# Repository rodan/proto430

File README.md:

## proto430

 ////// UNDER DEVELOPMENT ///////////////////////

 BoosterPack-compatible development boards used for quick prototyping and interfacing with i2c/spi/uart-based devices

```
 source:       https://github.com/rodan/proto430
 author:       Petre Rodan <2b4eda@subdimension.ro>
 license:      BSD
```

### Components

Collection of plug-in Booster-Pack PCBs compatible with the Texas Instruments LaunchPad development ecosystem. one board provides access to any 3v3 device via a serial interface, the other brings access to a graphical VFD display, a rotary encoder and also has infrared remote input. the two will be linked via i2c or spi.

project directory structure

 * ./hardware/display.* - eagle-based schematics and pcbs for the spi-based Noritake VFD 
 * ./hardware/sensor.*  - eagle-based schematics and pcbs for the i2c/spi/uart devboard
 * ./hardware/vfd.* - firmware for the display pcb

testing is done with MSP-EXP430FR5994 development kits

### Build requirements

you will need TI's excelent [GCC toolchain](https://www.ti.com/tool/MSP430-GCC-OPENSOURCE) or Code Composer Studio for linux and my [reference libraries for msp430 micros](https://github.com/rodan/atlas430) cloned in /opt/.

```
cd ./firmware
make
make install
```

the devboard has been modified by adding a 16MHz high frequency crystal and two load capacitors. if these components are missing from your board then make sure to disable the *USE_XT2* define from the Makefile or CCS.

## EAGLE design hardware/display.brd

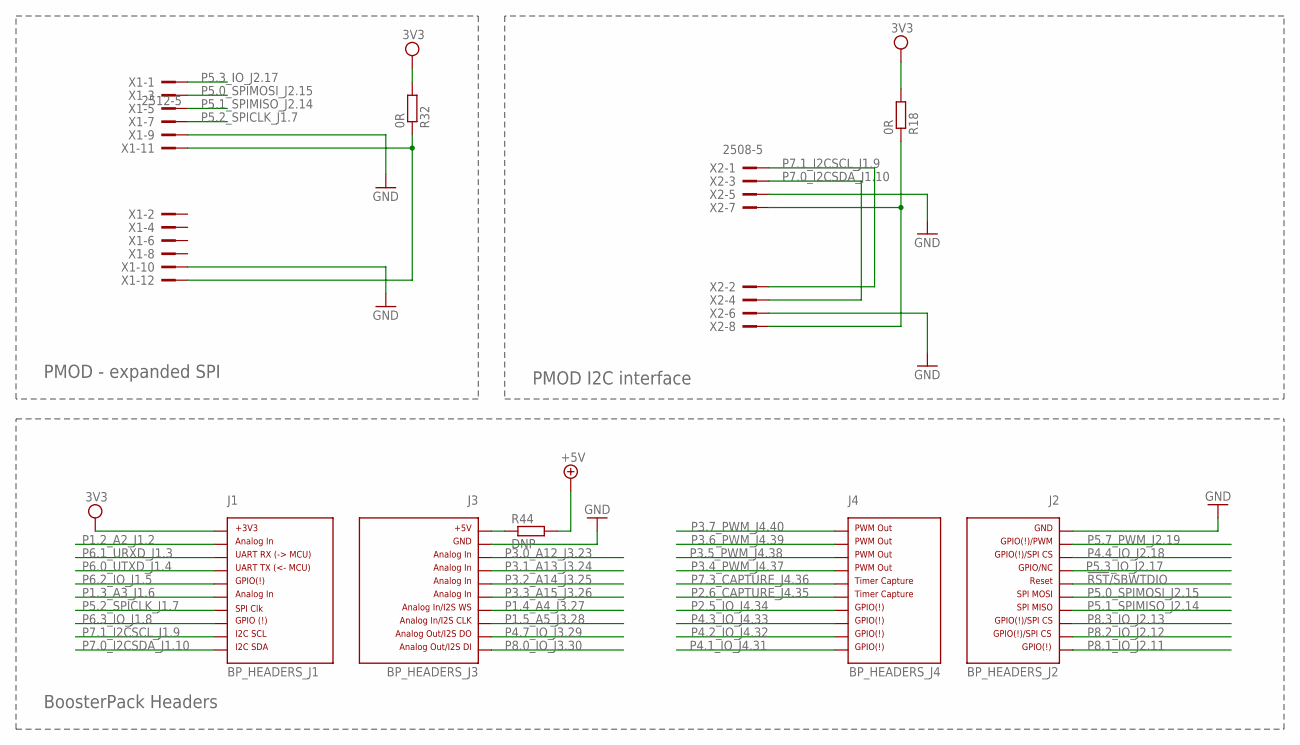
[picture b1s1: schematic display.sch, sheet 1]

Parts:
J1: BP_HEADERS_J1; J1
J2: BP_HEADERS_J2; J2
J3: BP_HEADERS_J3; J3
J4: BP_HEADERS_J4; J4
R18, R32: 0R; 0204V
R44: DNP; R0805W
X1: 2512-5; PAK100/2500-5-12
X2: 2508-5; PAK100/2500-5-08

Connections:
3V3: J1.1, R18.2, R32.2; also elsewhere on the board
!RST!/SBWTDIO: J2.16
+5V: R44.2; also elsewhere on the board
GND: J2.20, J3.22, X1.9, X1.10, X2.5, X2.6; also elsewhere on the board
unnamed: R18.1, X2.7, X2.8
unnamed: R32.1, X1.11, X1.12
unnamed: J3.21, R44.1
P1.2_A2_J1.2: J1.2; also elsewhere on the board
P1.3_A3_J1.6: J1.6; also elsewhere on the board
P1.4_A4_J3.27: J3.27; also elsewhere on the board
P1.5_A5_J3.28: J3.28; also elsewhere on the board
P2.5_IO_J4.34: J4.34; also elsewhere on the board
P2.6_CAPTURE_J4.35: J4.35; also elsewhere on the board
P3.0_A12_J3.23: J3.23; also elsewhere on the board
P3.1_A13_J3.24: J3.24; also elsewhere on the board
P3.2_A14_J3.25: J3.25; also elsewhere on the board
P3.3_A15_J3.26: J3.26; also elsewhere on the board
P3.4_PWM_J4.37: J4.37
P3.5_PWM_J4.38: J4.38
P3.6_PWM_J4.39: J4.39
P3.7_PWM_J4.40: J4.40
P4.1_IO_J4.31: J4.31
P4.2_IO_J4.32: J4.32
P4.3_IO_J4.33: J4.33
P4.4_IO_J2.18: J2.18; also elsewhere on the board
P4.7_IO_J3.29: J3.29
P5.0_SPIMOSI_J2.15: J2.15, X1.3; also elsewhere on the board
P5.1_SPIMISO_J2.14: J2.14, X1.5; also elsewhere on the board
P5.2_SPICLK_J1.7: J1.7, X1.7; also elsewhere on the board
P5.3_IO_J2.17: J2.17, X1.1
P5.7_PWM_J2.19: J2.19; also elsewhere on the board
P6.0_UTXD_J1.4: J1.4
P6.1_URXD_J1.3: J1.3
P6.2_IO_J1.5: J1.5
P6.3_IO_J1.8: J1.8; also elsewhere on the board
P7.0_I2CSDA_J1.10: J1.10, X2.3, X2.4; also elsewhere on the board
P7.1_I2CSCL_J1.9: J1.9, X2.1, X2.2; also elsewhere on the board
P7.3_CAPTURE_J4.36: J4.36; also elsewhere on the board
P8.0_IO_J3.30: J3.30
P8.1_IO_J2.11: J2.11; also elsewhere on the board
P8.2_IO_J2.12: J2.12; also elsewhere on the board
P8.3_IO_J2.13: J2.13; also elsewhere on the board

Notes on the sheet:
BoosterPack Headers
PMOD - expanded SPI
PMOD I2C interface

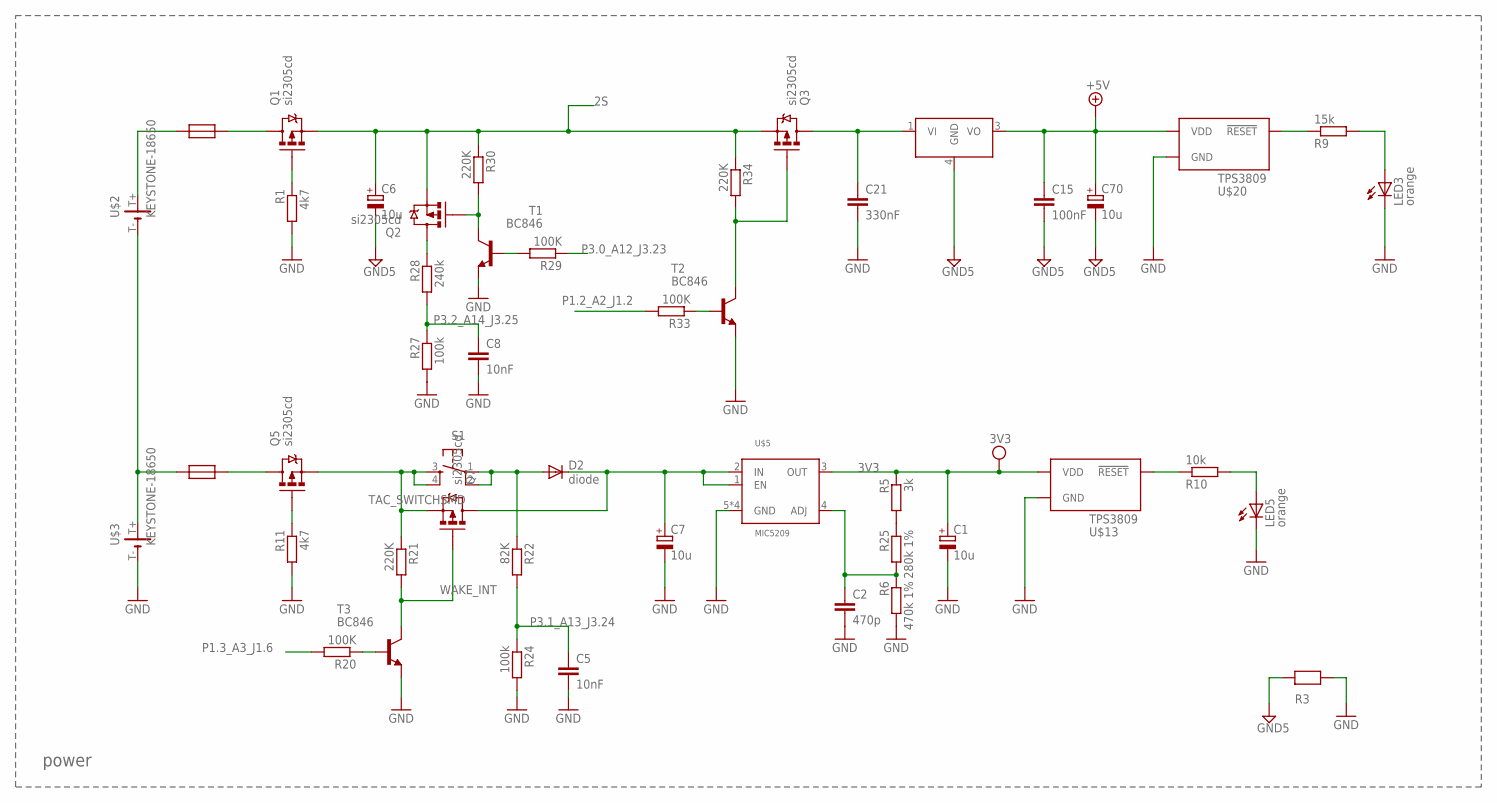
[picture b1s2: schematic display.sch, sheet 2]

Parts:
C1, C6, C7, C70: 10u; 153CLV-0405
C2: 470p; C0805
C5, C8: 10nF; C0805
C15: 100nF; C0805
C21: 330nF; C0805
D2: diode; SMA-DIODE
LED3, LED5: orange; CHIPLED_0805
Q1, Q2, Q3, Q5, Q7: si2305cd; SOT23-3_POWER
R1, R11: 4k7; R0805W
R3: 0R_0805; R0805W
R5: 3k; R0805W
R6: 470k 1%; R0805W
R9: 15k; R0805W
R10: 10k; R0805W
R20, R29, R33: 100K; R0805W
R21, R30, R34: 220K; R0805W
R22: 82K; R0805W
R24, R27: 100k; R0805W
R25: 280k 1%; R0805W
R28: 240k; R0805W
S1: TAC_SWITCHSMD; TACTILE-SWITCH-SMD
T1, T2, T3: BC846; SOT23
U4: 7805; D2PACK
U$2, U$3: KEYSTONE-18650; KEYSTONE_COMBO_18650
U$5: MIC5209; SO-08
U$7, U$8: Fuse 1A; 0805W
U$13, U$20: TPS3809; R_PDSO_G3

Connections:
2S: C6.+, Q1.2 (S), Q2.2 (S), Q3.2 (S), R30.1, R34.1; also elsewhere on the board
3V3: C1.+, R5.1, U$5.3 (OUT), U$13.P$3 (VDD); also elsewhere on the board
+5V: C15.1, C70.+, U4.3 (VO), U$20.P$3 (VDD); also elsewhere on the board
GND: C1.-, C2.2, C5.2, C7.-, C8.2, C21.2, LED3.C, LED5.C, R1.2, R3.2, R6.2, R11.2, R24.2, R27.2, T1.2 (E), T2.2 (E), T3.2 (E), U$3.T- (-), U$5.5 (GND), U$5.6 (GND), U$5.7 (GND), U$5.8 (GND), U$13.P$1 (GND), U$20.P$1 (GND); also elsewhere on the board
GND5: C6.-, C15.2, C70.-, R3.1, U4.4 (GND); also elsewhere on the board
unnamed: C21.1, Q3.3 (D), U4.1 (VI)
unnamed: Q1.1 (G), R1.1
unnamed: Q5.2 (S), Q7.2 (S), R21.1, S1.3, S1.4
unnamed: LED3.A, R9.2
unnamed: C2.1, R6.1, R25.2, U$5.4 (ADJ)
unnamed: Q1.3 (D), U$7.2
unnamed: Q5.3 (D), U$8.2
unnamed: R9.1, U$20.P$2 (!RESET)
unnamed: LED5.A, R10.2
unnamed: R10.1, U$13.P$2 (!RESET)
unnamed: C7.+, D2.C, Q7.3 (D), U$5.1 (EN), U$5.2 (IN)
unnamed: Q5.1 (G), R11.1
unnamed: R5.2, R25.1
unnamed: Q2.3 (D), R28.1
unnamed: Q2.1 (G), R30.2, T1.3 (C)
unnamed: R20.1, T3.1 (B)
unnamed: R29.2, T1.1 (B)
unnamed: R33.1, T2.1 (B)
unnamed: Q3.1 (G), R34.2, T2.3 (C)
N_BAT1: U$2.T- (-), U$3.T+ (+), U$8.1
N_BAT2: U$2.T+ (+), U$7.1
P1.2_A2_J1.2: R33.2; also elsewhere on the board
P1.3_A3_J1.6: R20.2; also elsewhere on the board
P3.0_A12_J3.23: R29.1; also elsewhere on the board
P3.1_A13_J3.24: C5.1, R22.2, R24.1; also elsewhere on the board
P3.2_A14_J3.25: C8.1, R27.1, R28.2; also elsewhere on the board
PUSH: D2.A, R22.1, S1.1, S1.2
WAKE_INT: Q7.1 (G), R21.2, T3.3 (C); also elsewhere on the board

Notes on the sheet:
power

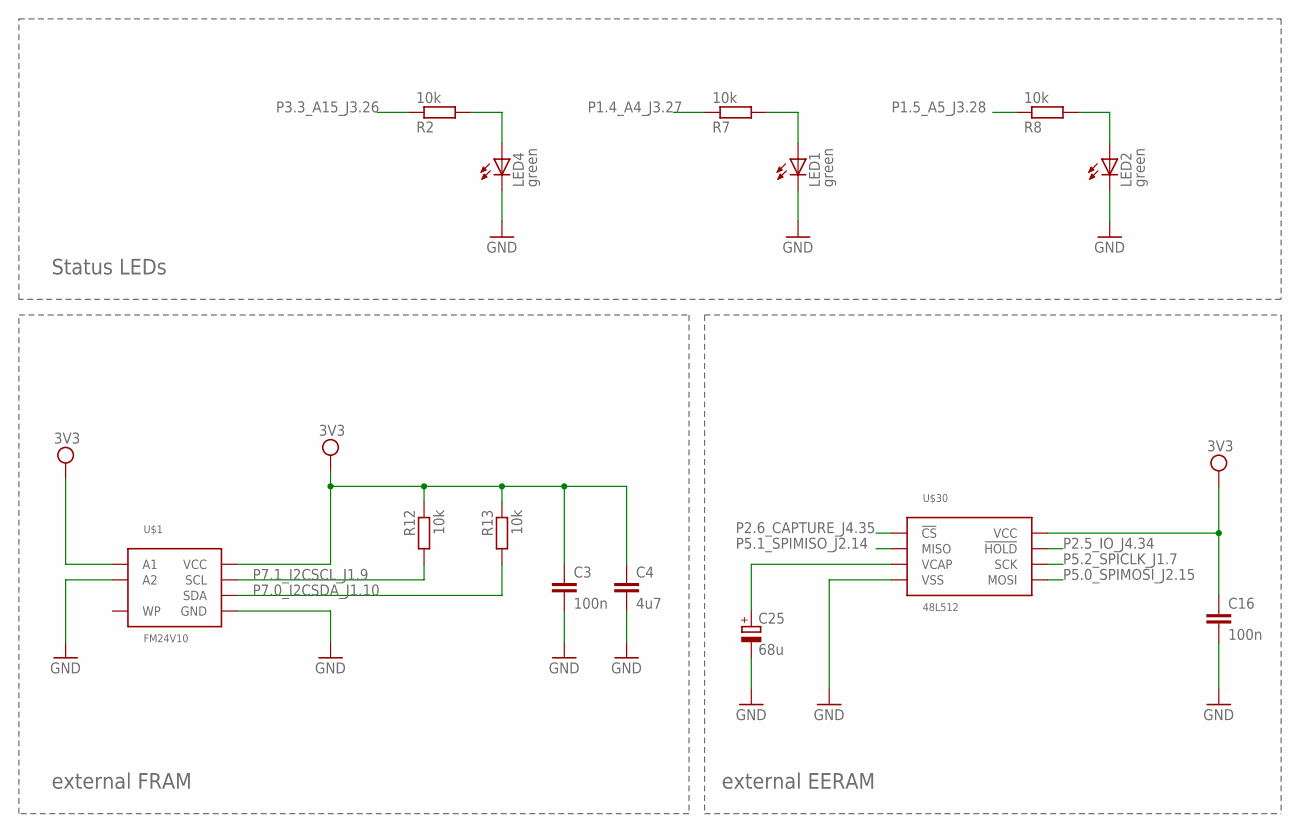
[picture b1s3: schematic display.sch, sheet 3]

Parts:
C3, C16: 100n; C0805
C4: 4u7; C0805
C25: 68u; SANYO-OSCON_SMD_C6
LED1, LED2, LED4: green; CHIPLED_0805
R2, R7, R8, R12, R13: 10k; R0805W
U$1: FM24V10; SO-08
U$30: 48L512; SO-08

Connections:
3V3: C3.1, C4.1, C16.1, R12.1, R13.1, U$1.2 (A1), U$1.8 (VCC), U$30.8 (VCC); also elsewhere on the board
GND: C3.2, C4.2, C16.2, C25.-, LED1.C, LED2.C, LED4.C, U$1.3 (A2), U$1.4 (GND), U$30.4 (VSS); also elsewhere on the board
unnamed: LED4.A, R2.2
unnamed: LED1.A, R7.2
unnamed: LED2.A, R8.2
unnamed: C25.+, U$30.3 (VCAP)
P1.4_A4_J3.27: R7.1; also elsewhere on the board
P1.5_A5_J3.28: R8.1; also elsewhere on the board
P2.5_IO_J4.34: U$30.7 (!HOLD); also elsewhere on the board
P2.6_CAPTURE_J4.35: U$30.1 (!CS); also elsewhere on the board
P3.3_A15_J3.26: R2.1; also elsewhere on the board
P5.0_SPIMOSI_J2.15: U$30.5 (MOSI); also elsewhere on the board
P5.1_SPIMISO_J2.14: U$30.2 (MISO); also elsewhere on the board
P5.2_SPICLK_J1.7: U$30.6 (SCK); also elsewhere on the board
P7.0_I2CSDA_J1.10: R13.2, U$1.5 (SDA); also elsewhere on the board
P7.1_I2CSCL_J1.9: R12.2, U$1.6 (SCL); also elsewhere on the board

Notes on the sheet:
external FRAM
Status LEDs
external EERAM

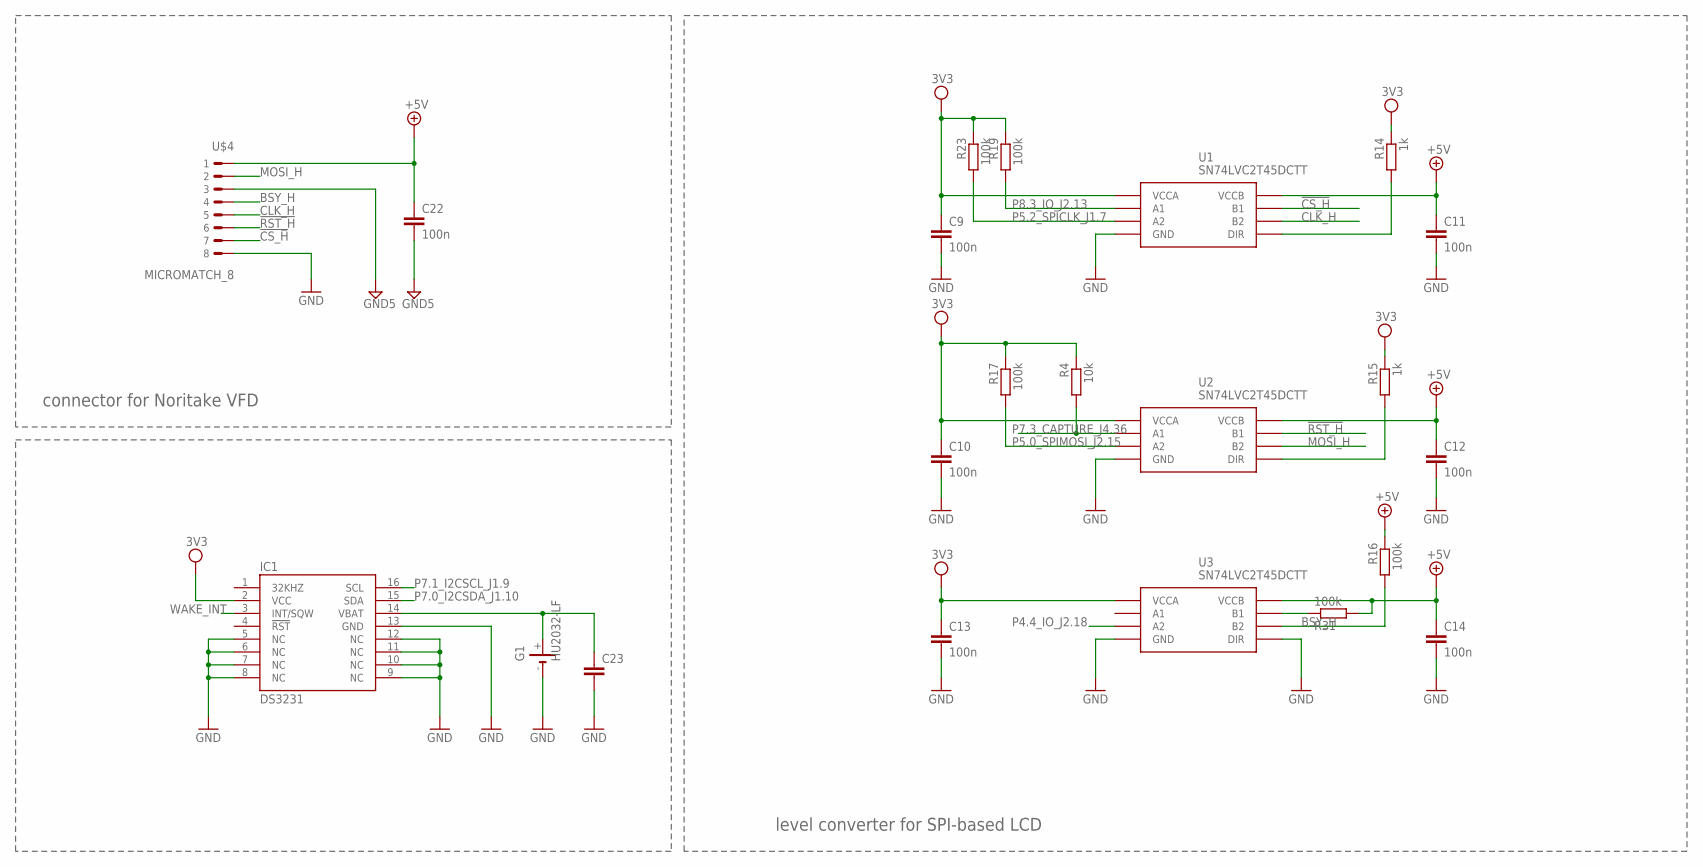
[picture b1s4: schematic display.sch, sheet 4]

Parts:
C9, C10, C11, C12, C13, C14, C22: 100n; C0805
C23: C-EU102-054X133; C102-054X133
G1: HU2032-LF
IC1: DS3231; SO-16
R4: 10k; R0805W
R14, R15: 1k; R0805W
R16, R17, R19, R23, R31: 100k; R0805W
U1, U2, U3: SN74LVC2T45DCTT; SSOP8
U$4: MICROMATCH_8; MICROMATCH8

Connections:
3V3: C9.1, C10.1, C13.1, IC1.2 (VCC), R4.1, R14.1, R15.1, R17.1, R19.1, R23.1, U1.P$1 (VCCA), U2.P$1 (VCCA), U3.P$1 (VCCA); also elsewhere on the board
!CS_H: U1.P$7 (B1), U$4.P$7 (7)
!RST_H: U2.P$7 (B1), U$4.P$6 (6)
+5V: C11.1, C12.1, C14.1, C22.1, R16.1, R31.2, U1.P$8 (VCCB), U2.P$8 (VCCB), U3.P$8 (VCCB), U$4.P$1 (1); also elsewhere on the board
BSY_H: R16.2, U3.P$6 (B2), U$4.P$4 (4)
CLK_H: U1.P$6 (B2), U$4.P$5 (5)
GND: C9.2, C10.2, C11.2, C12.2, C13.2, C14.2, C23.2, G1.-, IC1.5 (NC), IC1.6 (NC), IC1.7 (NC), IC1.8 (NC), IC1.9 (NC), IC1.10 (NC), IC1.11 (NC), IC1.12 (NC), IC1.13 (GND), U1.P$4 (GND), U2.P$4 (GND), U3.P$4 (GND), U3.P$5 (DIR), U$4.P$8 (8); also elsewhere on the board
GND5: C22.2, U$4.P$3 (3); also elsewhere on the board
MOSI_H: U2.P$6 (B2), U$4.P$2 (2)
unnamed: R14.2, U1.P$5 (DIR)
unnamed: R15.2, U2.P$5 (DIR)
unnamed: R31.1, U3.P$7 (B1)
unnamed: C23.1, G1.+, IC1.14 (VBAT)
P4.4_IO_J2.18: U3.P$3 (A2); also elsewhere on the board
P5.0_SPIMOSI_J2.15: R17.2, U2.P$3 (A2); also elsewhere on the board
P5.2_SPICLK_J1.7: R23.2, U1.P$3 (A2); also elsewhere on the board
P7.0_I2CSDA_J1.10: IC1.15 (SDA); also elsewhere on the board
P7.1_I2CSCL_J1.9: IC1.16 (SCL); also elsewhere on the board
P7.3_CAPTURE_J4.36: R4.2, U2.P$2 (A1); also elsewhere on the board
P8.3_IO_J2.13: R19.2, U1.P$2 (A1); also elsewhere on the board
WAKE_INT: IC1.3 (INT/SQW); also elsewhere on the board

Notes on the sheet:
connector for Noritake VFD
level converter for SPI-based LCD

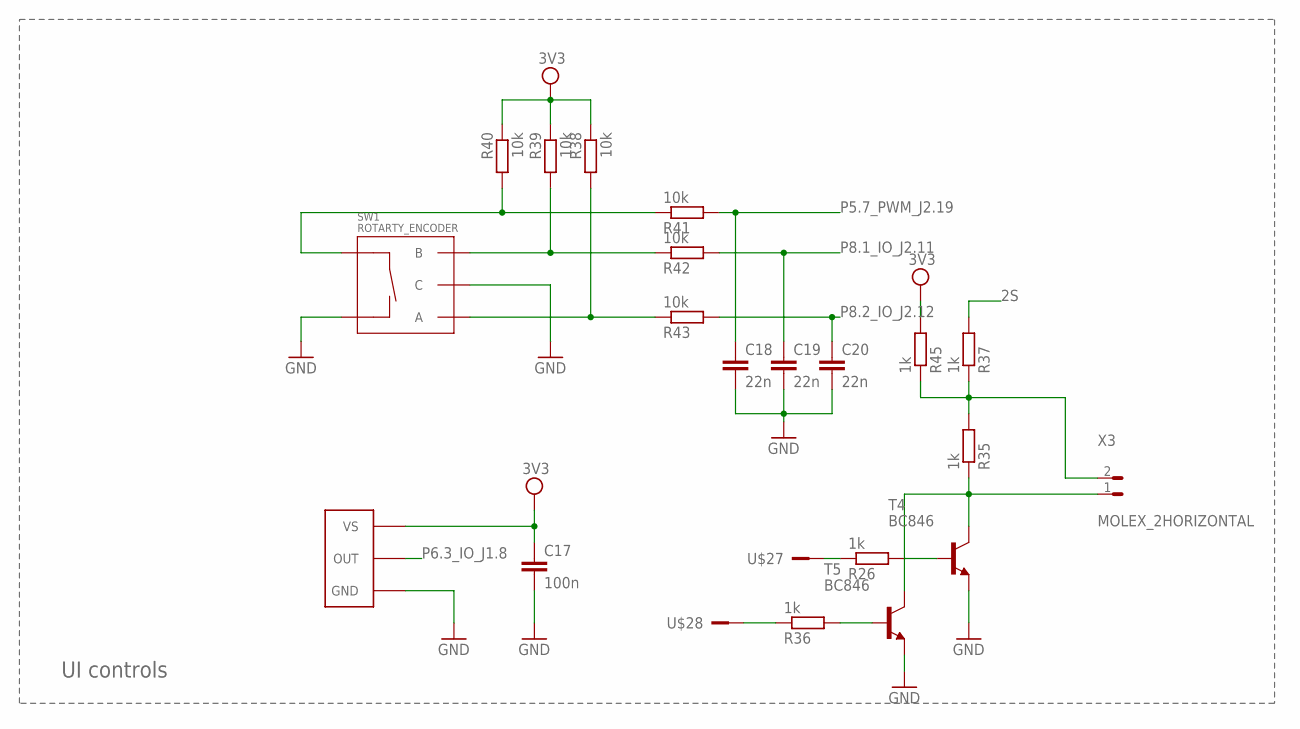
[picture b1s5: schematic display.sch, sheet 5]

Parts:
C17: 100n; C0805
C18, C19, C20: 22n; C0805
R26, R35, R36, R37, R45: 1k; R0805W
R38, R39, R40, R41, R42, R43: 10k; R0805W
SW1: ROTARTY_ENCODER; ROTARY_ENC_PLAIN
T4, T5: BC846; SOT23
U$26: TSOP36X; TSOP36X_SMD
U$27, U$28: TP; TP_THT
X3: MOLEX_2HORIZONTAL; 0530480210

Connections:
2S: R37.2; also elsewhere on the board
3V3: C17.1, R38.1, R39.1, R40.1, R45.2, U$26.P$3 (VS); also elsewhere on the board
GND: C17.2, C18.2, C19.2, C20.2, SW1.C, SW1.SW-, T4.2 (E), T5.2 (E), U$26.P$1 (GND); also elsewhere on the board
unnamed: R35.2, R37.1, R45.1, X3.2 (1)
unnamed: R26.2, T4.1 (B)
unnamed: R35.1, T4.3 (C), T5.3 (C), X3.1 (2)
unnamed: R26.1, U$27.1
unnamed: R40.2, R41.1, SW1.SW+
unnamed: R39.2, R42.1, SW1.B
unnamed: R38.2, R43.1, SW1.A
unnamed: R36.2, T5.1 (B)
unnamed: R36.1, U$28.1
P5.7_PWM_J2.19: C18.1, R41.2; also elsewhere on the board
P6.3_IO_J1.8: U$26.P$4 (OUT); also elsewhere on the board
P8.1_IO_J2.11: C19.1, R42.2; also elsewhere on the board
P8.2_IO_J2.12: C20.1, R43.2; also elsewhere on the board

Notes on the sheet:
UI controls

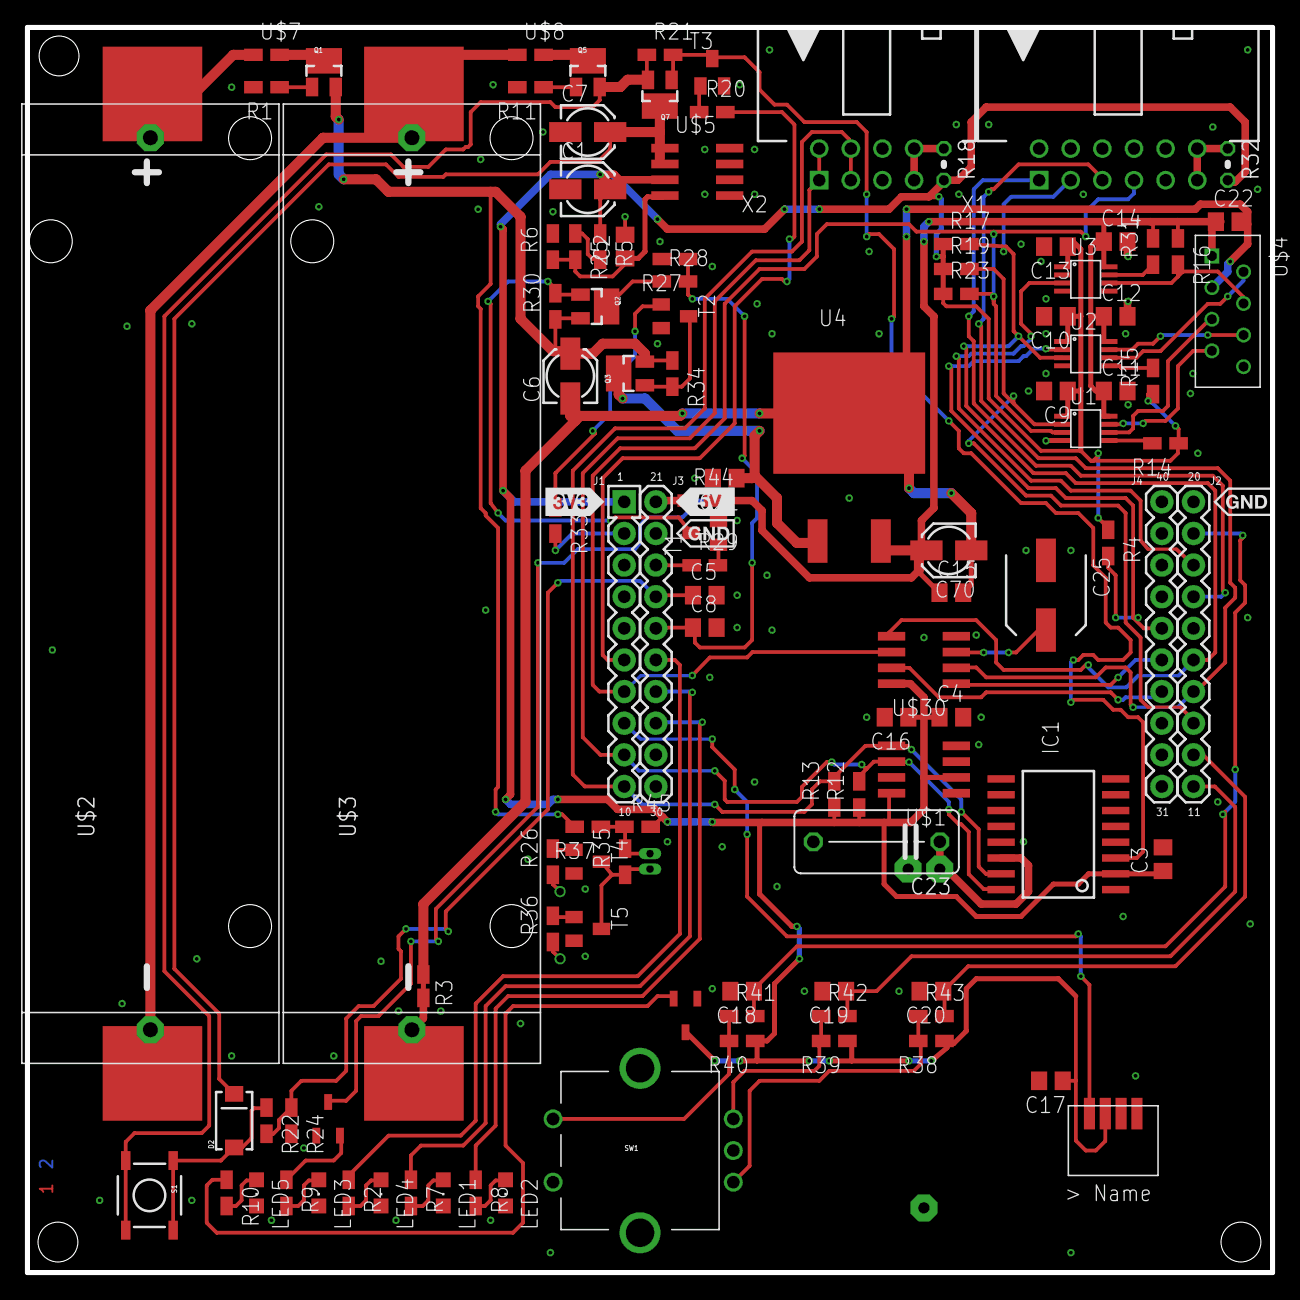
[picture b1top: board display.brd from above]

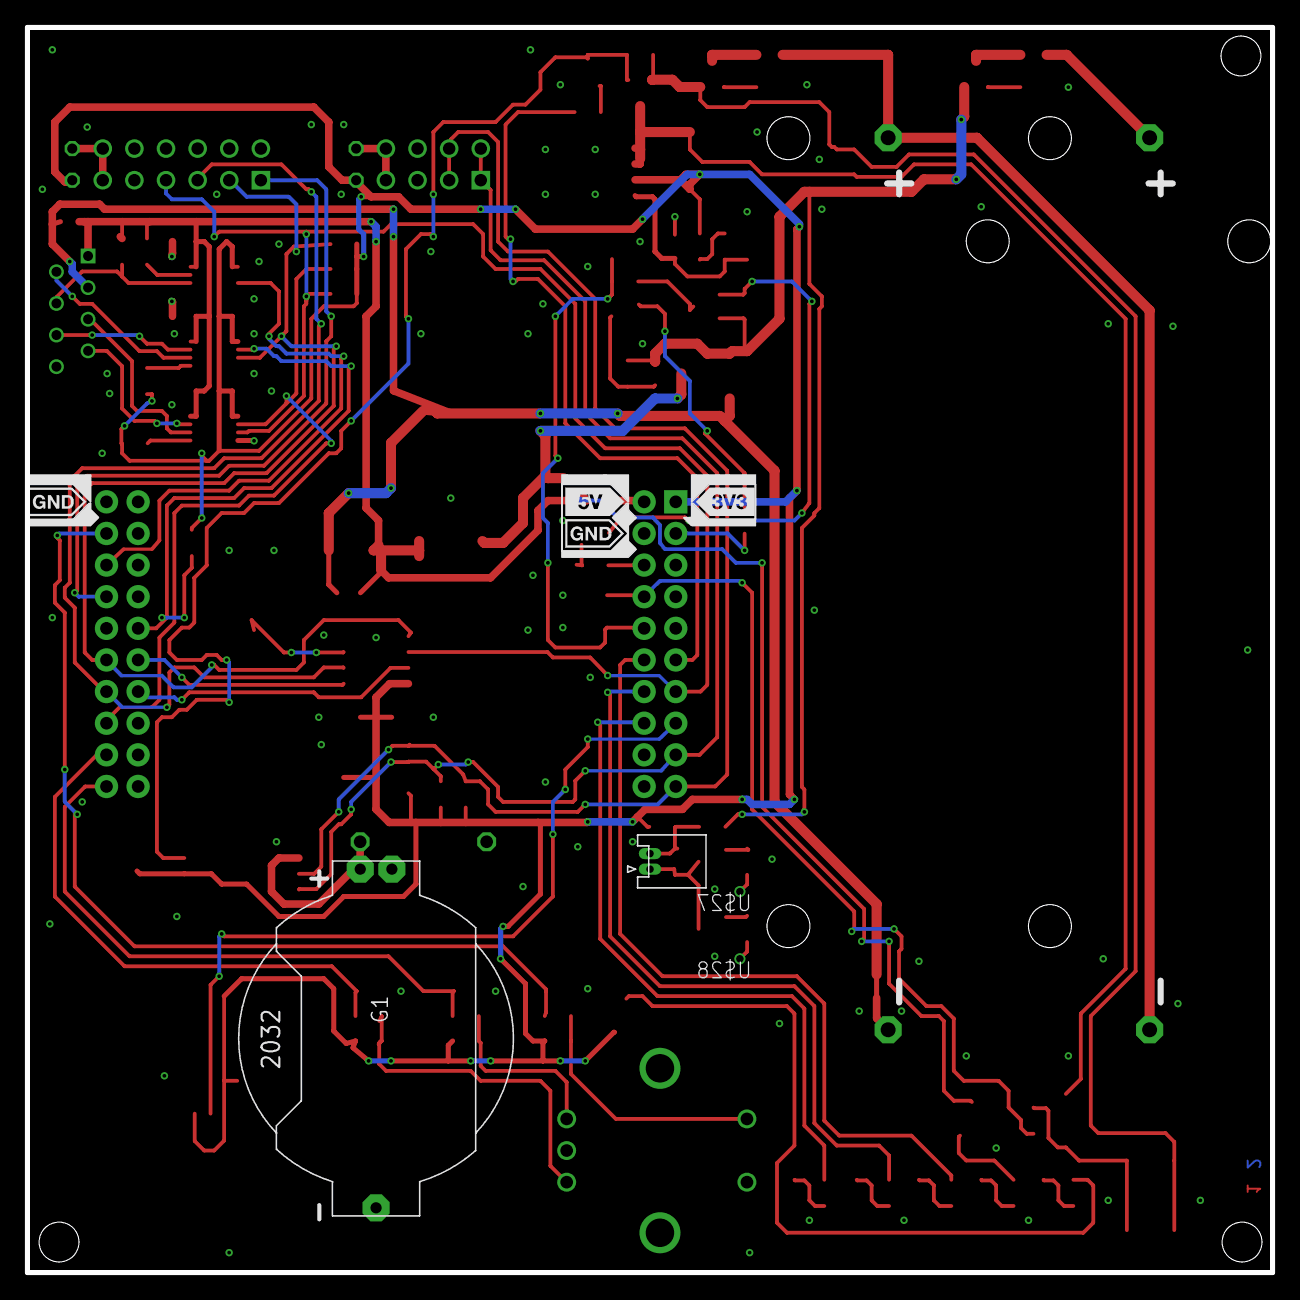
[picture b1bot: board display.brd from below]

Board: 2 copper layers, 100.0 x 100.0 mm, 114 parts (2 on the bottom side), 76 nets.

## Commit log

2022-03-04 initial import
2022-03-04 rtc works
2022-03-05 cleanup
2022-03-05 add rotary decoder
2022-03-06 add ir decoder
2022-03-06 make the rtc and the ir decoder optional
2022-03-07 vfd is working in ascii mode
2022-03-09 i2c and spi transactions have to be separated a few ms from each other
2022-03-13 add readme
2023-02-13 vfd related
2023-08-25 pins updated
2023-08-25 add i2c testing
2023-08-25 i2c-related updates
2023-10-17 pcb back from production, pin reconfiguration
2024-11-17 pin map update
2024-12-17 submodule testing
2024-12-17 cleanup: FreeBSD compat

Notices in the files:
parts and their libraries:
SparkFun-Electromechanical: Licensing: Creative Commons ShareAlike 4.0 International - https://creativecommons.org/licenses/by-sa/4.0
SparkFun-DiscreteSemi: Licensing: CC v3.0 Share-Alike You are welcome to use this library for commercial purposes.
